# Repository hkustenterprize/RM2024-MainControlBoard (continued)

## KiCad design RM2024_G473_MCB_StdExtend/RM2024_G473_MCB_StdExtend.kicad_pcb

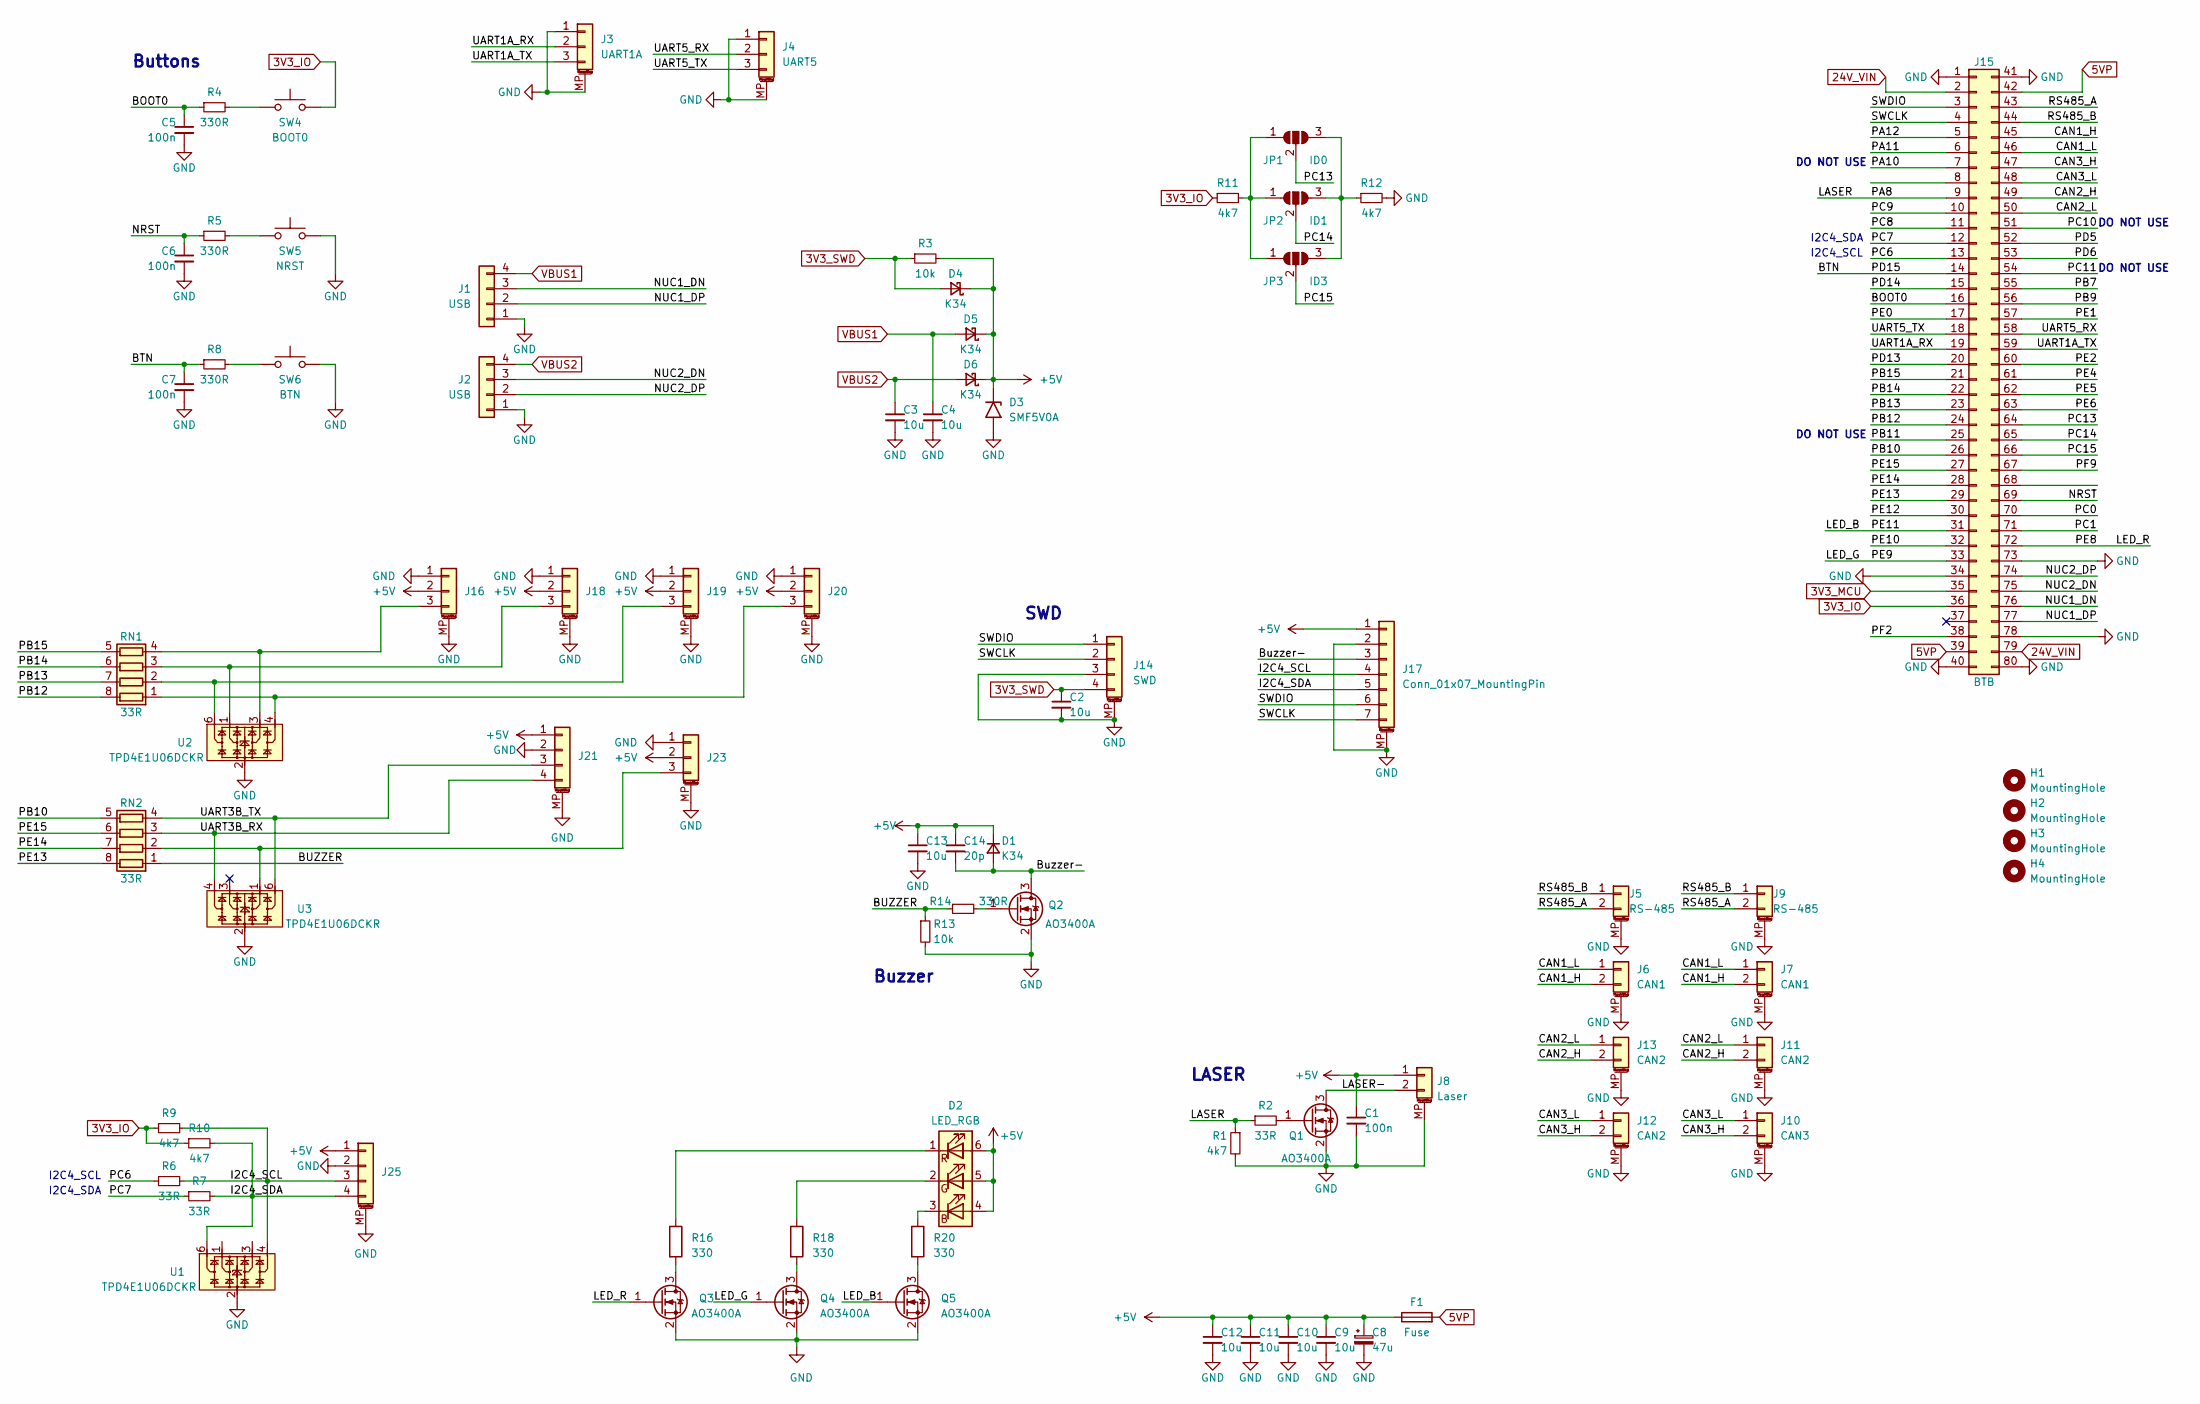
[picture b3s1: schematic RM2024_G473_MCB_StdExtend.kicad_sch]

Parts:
C1, C5, C6, C7: 100n; C_0603_1608Metric
C2, C3, C4, C9, C10, C11, C12, C13: 10u; C_0603_1608Metric
C8: 47u; CP_EIA-3216-18_Kemet-A_Pad1.58x1.35mm_HandSolder
C14: 20p; C_0603_1608Metric
D1, D4, D5, D6: K34; D_SMF
D2: LED_RGB; LED_RGB_5050-6
D3: SMF5V0A; D_SMF
F1: Fuse; Fuse_1206_3216Metric
H1, H2, H3, H4: MountingHole; MountingHole_3.2mm_M3_DIN965_Pad
J1, J2: USB; JST_PH_B4B-PH-K_1x04_P2.00mm_Vertical
J3: UART1A; JST_GH_BM03B-GHS-TBT_1x03-1MP_P1.25mm_Vertical
J4: UART5; JST_GH_BM03B-GHS-TBT_1x03-1MP_P1.25mm_Vertical
J5, J9: RS-485; JST_GH_BM02B-GHS-TBT_1x02-1MP_P1.25mm_Vertical
J6, J7: CAN1; JST_GH_BM02B-GHS-TBT_1x02-1MP_P1.25mm_Vertical
J8: Laser; Molex_PicoBlade_53398-0271_1x02-1MP_P1.25mm_Vertical
J10: CAN3; JST_GH_BM02B-GHS-TBT_1x02-1MP_P1.25mm_Vertical
J11, J12, J13: CAN2; JST_GH_BM02B-GHS-TBT_1x02-1MP_P1.25mm_Vertical
J14: SWD; Molex_PicoBlade_53398-0471_1x04-1MP_P1.25mm_Vertical
J15: BTB; BTB_P0.8mm_2x40pin_M
J16, J18, J19, J20, J23: Conn_01x03_MountingPin; JST_GH_BM03B-GHS-TBT_1x03-1MP_P1.25mm_Vertical
J17: Conn_01x07_MountingPin; JST_GH_BM07B-GHS-TBT_1x07-1MP_P1.25mm_Vertical
J21, J25: Conn_01x04_MountingPin; JST_GH_BM04B-GHS-TBT_1x04-1MP_P1.25mm_Vertical
JP1: ID0; SolderJumper-3_P1.3mm_Open_RoundedPad1.0x1.5mm_NumberLabels
JP2: ID1; SolderJumper-3_P1.3mm_Open_RoundedPad1.0x1.5mm_NumberLabels
JP3: ID3; SolderJumper-3_P1.3mm_Open_RoundedPad1.0x1.5mm_NumberLabels
Q1, Q2, Q3, Q4, Q5: AO3400A; SOT-23
R1, R9, R10, R11, R12: 4k7; R_0603_1608Metric
R2, R6, R7: 33R; R_0603_1608Metric
R3, R13: 10k; R_0603_1608Metric
R4, R5, R8, R14: 330R; R_0603_1608Metric
R16, R18, R20: 330; R_0603_1608Metric
RN1, RN2: 33R; R_Array_Concave_4x0603
SW4: BOOT0; SW_SPST_PTS810
SW5: NRST; SW_SPST_PTS810
SW6: BTN; SW_SPST_PTS810
U1, U2, U3: TPD4E1U06DCKR; SOT-363_SC-70-6

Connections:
3V3_IO: J15.36, R9.1, R10.1, R11.1, SW4.2
3V3_MCU: J15.35
3V3_SWD: C2.1, D4.2 (A), J14.4, R3.1
5VP: F1.2, J15.39, J15.42
24V_VIN: J15.2, J15.79
+5V: C1.1, C8.1, C9.1, C10.1, C11.1, C12.1, C13.1, C14.1, D1.1 (K), D2.4 (BA), D2.5 (GA), D2.6 (RA), D3.1 (A1), D4.1 (K), D5.1 (K), D6.1 (K), F1.1, J8.1, J16.2, J17.1, J18.2, J19.2, J20.2, J21.1, J23.2, J25.1, R3.2
/BOOT0: C5.1, J15.16, R4.1
/BTN: C7.1, J15.14, R8.1
/BUZZER: R13.1, R14.1, RN2.1 (R1.1)
/Buzzer-: C14.2, D1.2 (A), J17.3, Q2.3 (D)
/CAN1_H: J6.2, J7.2, J15.45
/CAN1_L: J6.1, J7.1, J15.46
/CAN2_H: J11.2, J13.2, J15.49
/CAN2_L: J11.1, J13.1, J15.50
/CAN3_H: J10.2, J12.2, J15.47
/CAN3_L: J10.1, J12.1, J15.48
/I2C4_SCL: J17.4, J25.3, R6.2, R9.2, U1.4
/I2C4_SDA: J17.5, J25.4, R7.2, R10.2, U1.6
/LASER: J15.9, R1.1, R2.1
/LASER-: J8.2, Q1.3 (D)
/LED_B: J15.31, Q5.1 (G)
/LED_G: J15.33, Q4.1 (G)
/LED_R: J15.72, Q3.1 (G)
/NRST: C6.1, J15.69, R5.1
/NUC1_DN: J1.3, J15.76
/NUC1_DP: J1.2, J15.77
/NUC2_DN: J2.3, J15.75
/NUC2_DP: J2.2, J15.74
/PA10: J15.7
/PA11: J15.6
/PA12: J15.5
/PB7: J15.55
/PB9: J15.56
/PB10: J15.26, RN2.5 (R4.2)
/PB11: J15.25
/PB12: J15.24, RN1.8 (R1.2)
/PB13: J15.23, RN1.7 (R2.2)
/PB14: J15.22, RN1.6 (R3.2)
/PB15: J15.21, RN1.5 (R4.2)
/PC0: J15.70
/PC1: J15.71
/PC6: J15.13, R6.1
/PC7: J15.12, R7.1
/PC8: J15.11
/PC9: J15.10
/PC10: J15.51
/PC11: J15.54
/PC13: J15.64, JP1.2 (C)
/PC14: J15.65, JP2.2 (C)
/PC15: J15.66, JP3.2 (C)
/PD5: J15.52
/PD6: J15.53
/PD13: J15.20
/PD14: J15.15
/PE0: J15.17
/PE1: J15.57
/PE2: J15.60
/PE4: J15.61
/PE5: J15.62
/PE6: J15.63
/PE10: J15.32
/PE12: J15.30
/PE13: J15.29, RN2.8 (R1.2)
/PE14: J15.28, RN2.7 (R2.2)
/PE15: J15.27, RN2.6 (R3.2)
/PF2: J15.38
/PF9: J15.67
/RS485_A: J5.2, J9.2, J15.43
/RS485_B: J5.1, J9.1, J15.44
/SWCLK: J14.2, J15.4, J17.7
/SWDIO: J14.1, J15.3, J17.6
/UART1A_RX: J3.2, J15.19
/UART1A_TX: J3.3, J15.59
/UART3B_RX: J21.4, RN2.3 (R3.1), U3.4
/UART3B_TX: J21.3, RN2.4 (R4.1), U3.6
/UART5_RX: J4.2, J15.58
/UART5_TX: J4.3, J15.18
GND: C1.2, C2.2, C3.2, C4.2, C5.2, C6.2, C7.2, C8.2, C9.2, C10.2, C11.2, C12.2, C13.2, D3.2 (A2), J1.1, J2.1, J3.1, J3.MP (MountPin), J4.1, J4.MP (MountPin), J5.MP (MountPin), J6.MP (MountPin), J7.MP (MountPin), J8.MP (MountPin), J9.MP (MountPin), J10.MP (MountPin), J11.MP (MountPin), J12.MP (MountPin), J13.MP (MountPin), J14.3, J14.MP (MountPin), J15.1, J15.34, J15.40, J15.41, J15.73, J15.78, J15.80, J16.1, J16.MP (MountPin), J17.2, J17.MP (MountPin), J18.1, J18.MP (MountPin), J19.1, J19.MP (MountPin), J20.1, J20.MP (MountPin), J21.2, J21.MP (MountPin), J23.1, J23.MP (MountPin), J25.2, J25.MP (MountPin), Q1.2 (S), Q2.2 (S), Q3.2 (S), Q4.2 (S), Q5.2 (S), R1.2, R12.2, R13.2, SW5.2, SW6.2, U1.2, U2.2, U3.2
unnamed: D2.3 (BK), R20.1
unnamed: D2.2 (GK), R18.1
unnamed: D2.1 (RK), R16.1
unnamed: J16.3, RN1.4 (R4.1), U2.3
unnamed: J18.3, RN1.3 (R3.1), U2.1
unnamed: J19.3, RN1.2 (R2.1), U2.6
unnamed: J20.3, RN1.1 (R1.1), U2.4
unnamed: J23.3, RN2.2 (R2.1), U3.1
unnamed: JP1.1 (A), JP2.1 (A), JP3.1 (A), R11.2
unnamed: JP1.3 (B), JP2.3 (B), JP3.3 (B), R12.1
unnamed: Q1.1 (G), R2.2
unnamed: Q2.1 (G), R14.2
unnamed: Q3.3 (D), R16.2
unnamed: Q4.3 (D), R18.2
unnamed: Q5.3 (D), R20.2
unnamed: R4.2, SW4.1
unnamed: R5.2, SW5.1
unnamed: R8.2, SW6.1
VBUS1: C4.1, D5.2 (A), J1.4
VBUS2: C3.1, D6.2 (A), J2.4

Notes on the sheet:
DO NOT USE
I2C4_SDA
Buttons
SWD
I2C4_SCL
LASER
Buzzer

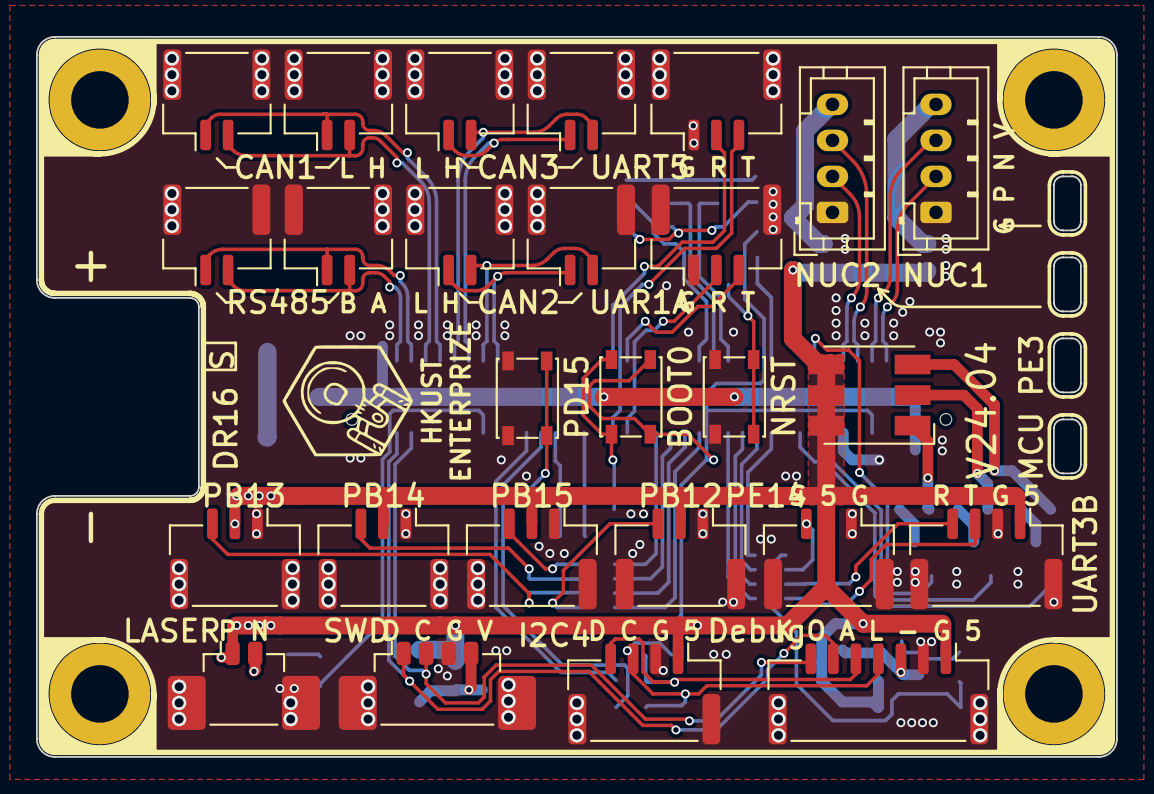
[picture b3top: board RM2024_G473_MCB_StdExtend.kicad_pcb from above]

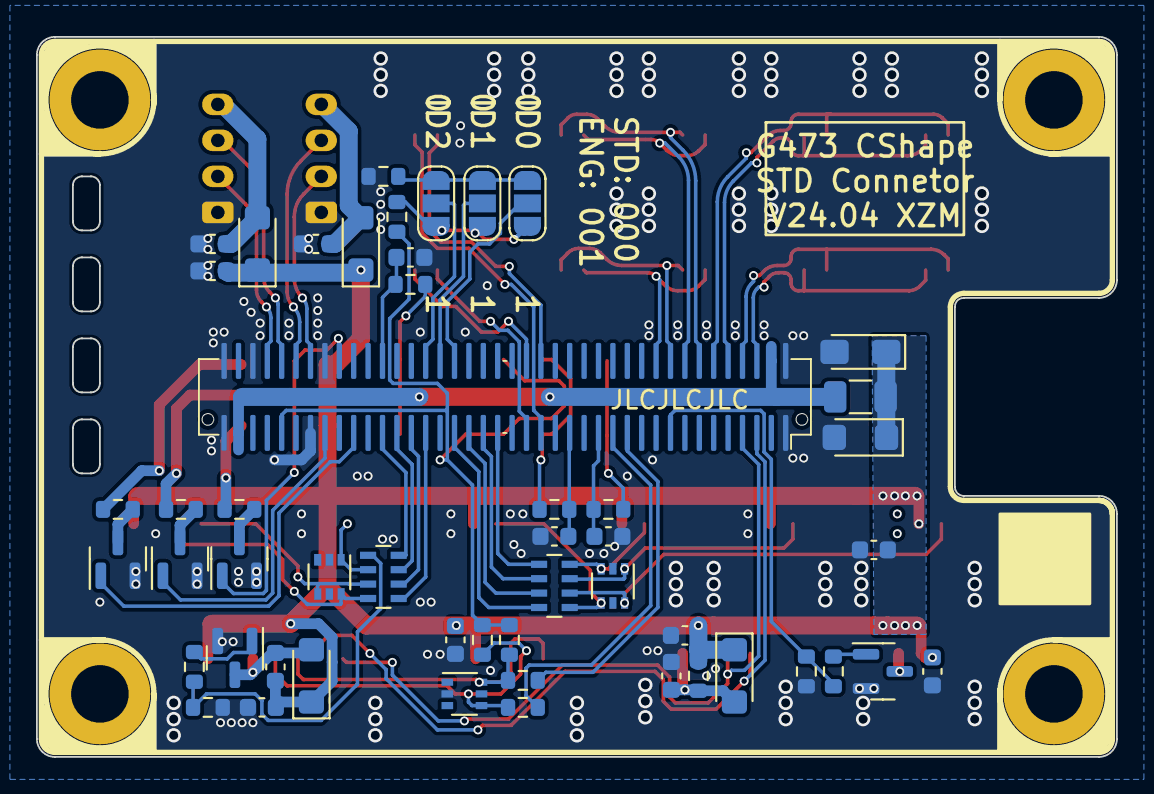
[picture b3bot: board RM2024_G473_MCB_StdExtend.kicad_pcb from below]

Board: 2 copper layers, 60.0 x 40.0 mm, 81 parts (50 on the bottom side), 71 nets.

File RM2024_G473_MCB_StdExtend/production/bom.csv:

Designator,Footprint,Quantity,Value,LCSC Part #
"C1, C5, C6, C7",0603,4,100n,
"C10, C11, C12, C13, C2, C3, C4, C9",0603,8,10u,
C14,0603,1,20p,
C8,CP_EIA-3216-18_Kemet-A_Pad1.58x1.35mm_HandSolder,1,47u,
"D1, D4, D5, D6",D_SMF,4,K34,
D2,LED_RGB_5050-6,1,LED_RGB,
D3,D_SMF,1,SMF5V0A,
F1,1206,1,Fuse,
"H1, H2, H3, H4",MountingHole_3.2mm_M3_DIN965_Pad,4,MountingHole,
"J1, J2",JST_PH_B4B-PH-K_1x04_P2.00mm_Vertical,2,USB,
J10,JST_GH_BM02B-GHS-TBT_1x02-1MP_P1.25mm_Vertical,1,CAN3,
"J11, J12, J13",JST_GH_BM02B-GHS-TBT_1x02-1MP_P1.25mm_Vertical,3,CAN2,
J14,Molex_PicoBlade_53398-0471_1x04-1MP_P1.25mm_Vertical,1,SWD,
J15,BTB_P0.8mm_2x40pin_M,1,BTB,
"J16, J18, J19, J20, J23",JST_GH_BM03B-GHS-TBT_1x03-1MP_P1.25mm_Vertical,5,Conn_01x03_MountingPin,
J17,JST_GH_BM07B-GHS-TBT_1x07-1MP_P1.25mm_Vertical,1,Conn_01x07_MountingPin,
"J21, J25",JST_GH_BM04B-GHS-TBT_1x04-1MP_P1.25mm_Vertical,2,Conn_01x04_MountingPin,
J3,JST_GH_BM03B-GHS-TBT_1x03-1MP_P1.25mm_Vertical,1,UART1A,
J4,JST_GH_BM03B-GHS-TBT_1x03-1MP_P1.25mm_Vertical,1,UART5,
"J5, J9",JST_GH_BM02B-GHS-TBT_1x02-1MP_P1.25mm_Vertical,2,RS-485,
"J6, J7",JST_GH_BM02B-GHS-TBT_1x02-1MP_P1.25mm_Vertical,2,CAN1,
J8,Molex_PicoBlade_53398-0271_1x02-1MP_P1.25mm_Vertical,1,Laser ,
JP1,SolderJumper-3_P1.3mm_Open_RoundedPad1.0x1.5mm_NumberLabels,1,ID0,
JP2,SolderJumper-3_P1.3mm_Open_RoundedPad1.0x1.5mm_NumberLabels,1,ID1,
JP3,SolderJumper-3_P1.3mm_Open_RoundedPad1.0x1.5mm_NumberLabels,1,ID3,
"Q1, Q2, Q3, Q4, Q5",SOT-23,5,AO3400A,
"R1, R10, R11, R12, R9",0603,5,4k7,
"R13, R3",0603,2,10k,
"R14, R4, R5, R8",0603,4,330R,
"R16, R18, R20",0603,3,330,
"R2, R6, R7",0603,3,33R,
"RN1, RN2",R_Array_Concave_4x0603,2,33R,
SW4,SW_SPST_PTS810,1,BOOT0,
SW5,SW_SPST_PTS810,1,NRST,
SW6,SW_SPST_PTS810,1,BTN,
"U1, U2, U3",SOT-363_SC-70-6,3,TPD4E1U06DCKR,

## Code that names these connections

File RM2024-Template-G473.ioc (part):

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Mcu.Name=STM32G473V(B-C-E)Tx
Mcu.Package=LQFP100
Mcu.UserName=STM32G473VETx
PA0.Mode=CTS_RTS
PA0.Signal=USART2_CTS
PA1.Mode=CTS_RTS
PA1.Signal=USART2_RTS
PA10.GPIOParameters=GPIO_Label
PA10.GPIO_Label=UART1C_RX
PA10.Mode=Asynchronous
PA10.Signal=USART1_RX
PA13.Mode=Serial_Wire
PA13.Signal=SYS_JTMS-SWDIO
PA14.Mode=Serial_Wire
PA14.Signal=SYS_JTCK-SWCLK
PA15.GPIOParameters=GPIO_Label
PA15.GPIO_Label=UART4_DE
PA15.Mode=Hardware Flow Control (RS485)
PA15.Signal=UART4_DE
PA2.GPIOParameters=GPIO_Label
PA2.GPIO_Label=UART2A_TX
PA2.Mode=Asynchronous
PA2.Signal=USART2_TX
PA3.GPIOParameters=GPIO_Label
PA3.GPIO_Label=UART2A_RX
PA3.Mode=Asynchronous
PA3.Signal=USART2_RX
PA4.GPIOParameters=GPIO_Label
PA4.GPIO_Label=LIS3_CS
PA4.Signal=GPIO_Output
PA5.Mode=Full_Duplex_Master
PA5.Signal=SPI1_SCK
PA6.Mode=Full_Duplex_Master
PA6.Signal=SPI1_MISO
PA7.Mode=Full_Duplex_Master
PA7.Signal=SPI1_MOSI
PB0.GPIOParameters=GPIO_Label
PB0.GPIO_Label=LIS3_DRY
PB0.Signal=GPXTI0
PB1.GPIOParameters=GPIO_Label
PB1.GPIO_Label=ICM_DRY
PB1.Signal=GPXTI1
PB10.GPIOParameters=GPIO_Label
PB10.GPIO_Label=UART3B_TX
PB10.Signal=GPIO_Output
PB12.Signal=SPI2_NSS
PB13.Signal=SPI2_SCK
PB14.Signal=SPI2_MISO
PB15.Signal=SPI2_MOSI
PB2.GPIOParameters=GPIO_Label
PB2.GPIO_Label=ICM_CS
PB2.Signal=GPIO_Output
PB3.Mode=FDCAN_Activate
PB3.Signal=FDCAN3_RX
PB4.Mode=FDCAN_Activate
PB4.Signal=FDCAN3_TX
PB5.Mode=FDCAN_Activate
PB5.Signal=FDCAN2_RX
PB6.Mode=FDCAN_Activate
PB6.Signal=FDCAN2_TX
PB8-BOOT0.GPIOParameters=GPIO_Label
PB8-BOOT0.GPIO_Label=BOOT0
PB8-BOOT0.Signal=GPIO_Input
PC0.GPIOParameters=GPIO_Label
PC0.GPIO_Label=ADC_POWER
PC0.Signal=GPIO_Output
PC1.GPIOParameters=GPIO_Label
PC1.GPIO_Label=ADC_5V
PC1.Signal=GPIO_Output
PC10.GPIOParameters=GPIO_Label
PC10.GPIO_Label=UART4_TX
PC10.Mode=Asynchronous
PC10.Signal=UART4_TX
PC11.GPIOParameters=GPIO_Label
PC11.GPIO_Label=UART4_RX
PC11.Mode=Asynchronous
PC11.Signal=UART4_RX
PC12.GPIOParameters=GPIO_Label
PC12.GPIO_Label=UART5_TX
PC12.Mode=Asynchronous
PC12.Signal=UART5_TX
PC15-OSC32_OUT.GPIOParameters=GPIO_Label
PC15-OSC32_OUT.GPIO_Label=LASER
PC15-OSC32_OUT.Signal=GPIO_Output
PC2.GPIOParameters=GPIO_Label
PC2.GPIO_Label=BUTTON
PC2.Signal=GPIO_Output
PC3.GPIOParameters=GPIO_Label
PC3.GPIO_Label=BUZZER
PC3.Signal=GPIO_Output
PD0.Mode=FDCAN_Activate
PD0.Signal=FDCAN1_RX
PD1.Mode=FDCAN_Activate
PD1.Signal=FDCAN1_TX
PD11.Mode=CTS_RTS
PD11.Signal=USART3_CTS
PD12.Mode=CTS_RTS
PD12.Signal=USART3_RTS
PD2.GPIOParameters=GPIO_Label
PD2.GPIO_Label=UART5_RX
PD2.Mode=Asynchronous
PD2.Signal=UART5_RX
PD5.GPIOParameters=GPIO_Label
PD5.GPIO_Label=UART2B_TX
PD5.Signal=GPIO_Output
PD6.GPIOParameters=GPIO_Label
PD6.GPIO_Label=UART2B_RX
PD6.Signal=GPIO_Input
PD8.Mode=Asynchronous
PD8.Signal=USART3_TX
PD9.Mode=Asynchronous
PD9.Signal=USART3_RX
PE0.GPIOParameters=GPIO_Label
PE0.GPIO_Label=UART1B_TX
PE0.Mode=Asynchronous
PE0.Signal=USART1_TX
PE15.GPIOParameters=GPIO_Label
PE15.GPIO_Label=UART3B_RX
PE15.Signal=GPIO_Input
PE3.GPIOParameters=GPIO_Label
PE3.GPIO_Label=LED_ACT
PE3.Signal=GPIO_Output
PF0-OSC_IN.Mode=HSE-External-Oscillator
PF0-OSC_IN.Signal=RCC_OSC_IN
PF1-OSC_OUT.Mode=HSE-External-Oscillator
PF1-OSC_OUT.Signal=RCC_OSC_OUT
PF2.GPIOParameters=GPIO_Label
PF2.GPIO_Label=IMU_HEAT
PF2.Signal=S_TIM20_CH3
PG10-NRST.GPIOParameters=GPIO_Label
PG10-NRST.GPIO_Label=NRST
PG10-NRST.Mode=Clock-out
PG10-NRST.Signal=RCC_MCO
RCC.HSE_VALUE=25000000
RCC.SYSCLKFreq_VALUE=170000000
RCC.SYSCLKSource=RCC_SYSCLKSOURCE_PLLCLK
board=custom

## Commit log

2024-09-19 v0.5
2024-09-19 v0.51
2024-09-19 v0.6
2024-09-19 v0.61
2024-09-19 v0.62
2024-09-20 V0.9
2024-09-20 public
2024-09-20 public v1.1
